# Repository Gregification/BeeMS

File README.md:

# BeeMS
Battery Management System (BMS)

__a work in progress__

BMS for University Of Texas At Arlington's FSAE Race team's E27 vehicle.
> point of contact for this repo is <a href="https://github.com/gregclacker"> George Boone</a>

## Development
- Code Composer Studio 12
    - dependency on Driver Lib
    - projects are stand alone, no dependencies on other projects in this repo.
- Kicad 9
    - common symbol and footprint library shared amongst all Kicad projects. "zzLocal".

---
<i>
    <a href="https://github.com/goerge">goerge (Gorge Albrecht)</a> is not in any way involved or associated with this project. that account was accidentally listed as a contributor because of a typo in the spelling of <a href="https://github.com/gregclacker">george (George Boone)</a>.
</i>

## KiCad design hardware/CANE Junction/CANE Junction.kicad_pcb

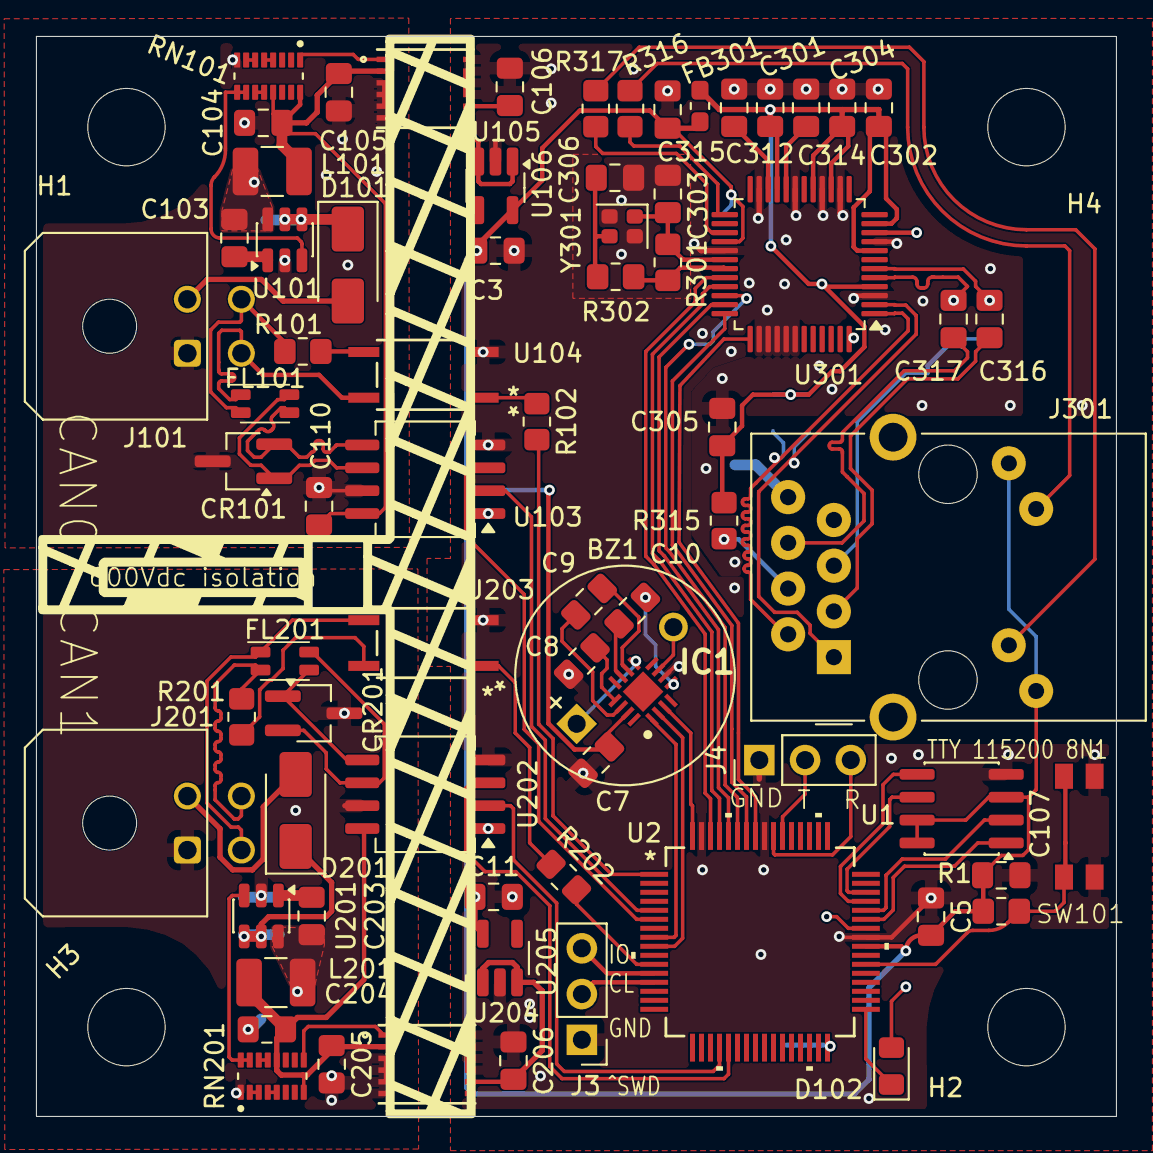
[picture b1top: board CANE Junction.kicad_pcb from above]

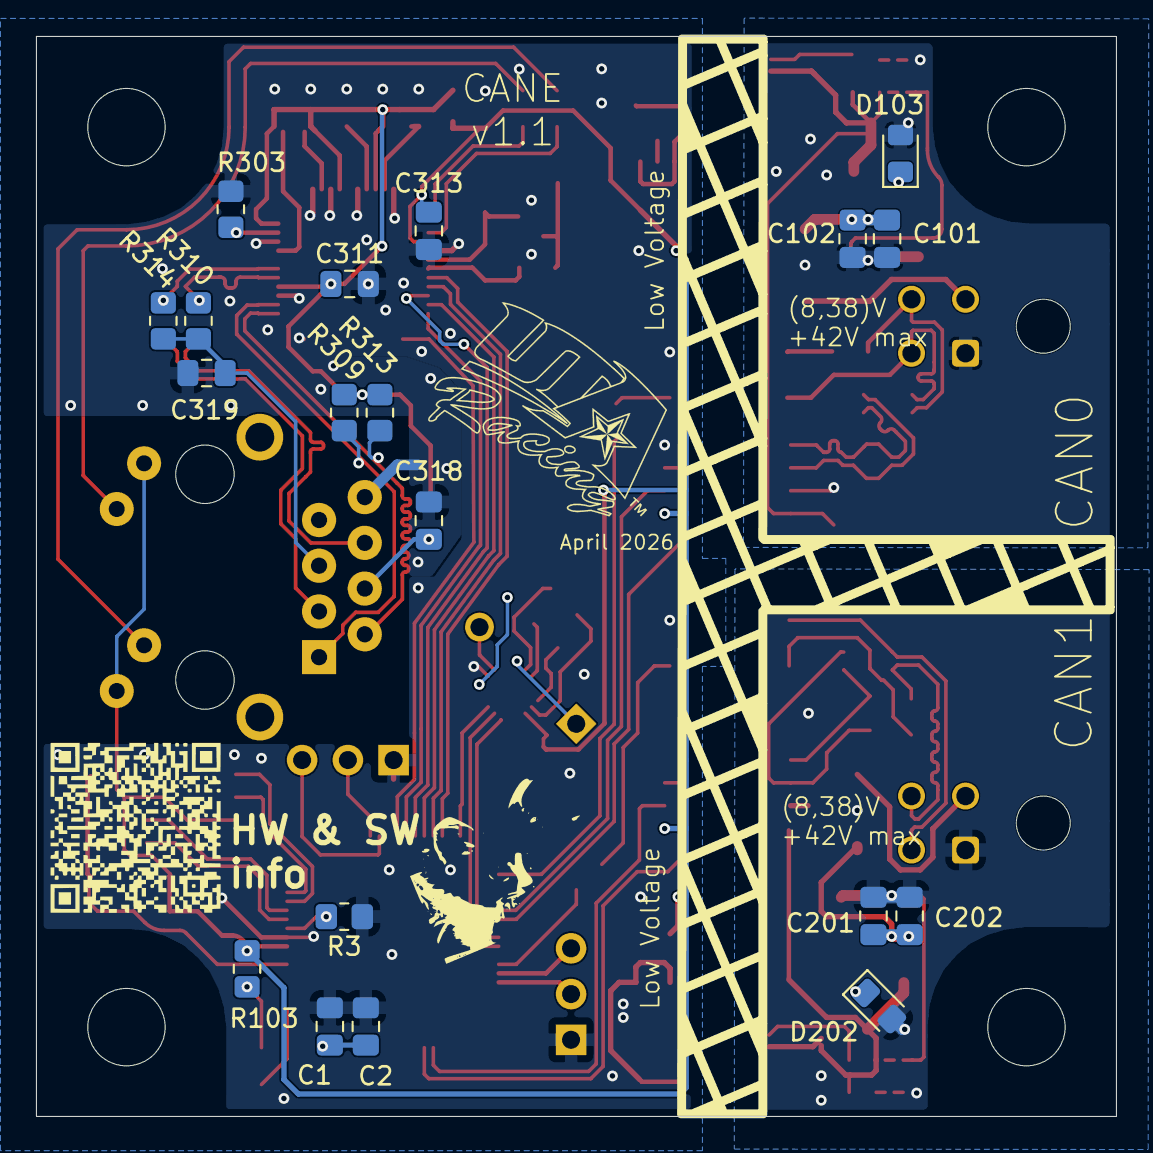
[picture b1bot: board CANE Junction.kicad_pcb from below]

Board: 2 copper layers, 60.0 x 60.0 mm, 95 parts (19 on the bottom side), 92 nets.

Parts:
BZ1: Buzzer; MagneticBuzzer_ProSignal_ABI-009-RC
C1, C2, C3, C11, C101, C102, C201, C202: 470n; C_0805_2012Metric_Pad1.18x1.45mm_HandSolder
C5, C7, C104, C105, C106, C204, C205, C206, C302: 22u; C_0805_2012Metric_Pad1.18x1.45mm_HandSolder
C8, C9, C10: 100n; C_0805_2012Metric_Pad1.18x1.45mm_HandSolder
C103, C107, C110, C203, C301, C304, C305, C311, C313, C315: 220n; C_0805_2012Metric_Pad1.18x1.45mm_HandSolder
C303, C306: 18p; C_0805_2012Metric_Pad1.18x1.45mm_HandSolder
C312, C319: 10n; C_0805_2012Metric_Pad1.18x1.45mm_HandSolder
C314: 4.7u; C_0805_2012Metric_Pad1.18x1.45mm_HandSolder
C316, C317: 6.8n; C_0805_2012Metric_Pad1.18x1.45mm_HandSolder
C318: 22n; C_0805_2012Metric_Pad1.18x1.45mm_HandSolder
CR101, CR201: ESD2CAN36DBZRQ1; TSOT-23_HandSoldering
D101, D201: ES1D; D_SMA
D102: blue; LED_0805_2012Metric_Pad1.15x1.40mm_HandSolder
D103, D202: TS4148; D_0805_2012Metric_Pad1.15x1.40mm_HandSolder
FB301: MH1608-151Y; L_0603_1608Metric_Pad1.05x0.95mm_HandSolder
FL101, FL201: Choke_CommonMode_FerriteCore_1243; L_CommonMode_Wurth_WE-CNSW-1206
H1, H2, H3, H4: MountingHole; MountingHole_4.3mm_M4_ISO7380
IC1: PAM8904QJER; QFN50P300X300X65-17N-D
J3: programming; PinHeader_1x03_P2.54mm_Vertical
J4: UART; PinHeader_1x03_P2.54mm_Vertical
J101, J201: glv; Molex_Micro-Fit_3.0_43045-0400_2x02_P3.00mm_Horizontal
J301: RJ45_Amphenol_RJMG1BD3B8K1ANR
L101, L201: 10u; L_1210_3225Metric_Pad1.42x2.65mm_HandSolder
R1, R3: 100k; R_0805_2012Metric_Pad1.20x1.40mm_HandSolder
R101, R201: 121; R_0805_2012Metric_Pad1.20x1.40mm_HandSolder
R102, R202, R316, R317: 750; R_0805_2012Metric_Pad1.20x1.40mm_HandSolder
R103: 2.4k; R_0805_2012Metric_Pad1.20x1.40mm_HandSolder
R301: 1M; R_0805_2012Metric_Pad1.20x1.40mm_HandSolder
R302, R315: 10; R_0805_2012Metric_Pad1.20x1.40mm_HandSolder
R303: 12.4k; R_0805_2012Metric_Pad1.20x1.40mm_HandSolder
R309, R310, R313, R314: 49.9; R_0805_2012Metric_Pad1.20x1.40mm_HandSolder
RN101, RN201: 20k; R_array_EXB2HV_8
SW101: SW_Push; wurth elektronik 4.7x3.5mm side push button
U1: MX25L3233FM2; SOIC-8_3.9x4.9mm_P1.27mm
U2: XMSPM0G3519SPMR; LQFP64_PM_TEX-M
U101, U201: AP64060ZQ; TSOT-23-6
U103, U202: ISO1044BD; SOIC-8_5.3x6.2mm_P1.27mm
U104, U203: ISOM8600; SOIC4_DFG_TEX-M
U105, U204: PUCC33420QRAQRQ1; VSON-FCRLF12_RAQ_TEX
U106, U205: NCP163ASN330T1G; SOT-23-5_HandSoldering
U301: W5500; LQFP-48_7x7mm_P0.5mm
Y301: Crystal_GND24; Crystal_SMD_2016-4Pin_2.0x1.6mm

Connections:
+3.3V: C3.1, C5.2, C7.1, C11.1, C107.2, C313.1, C315.1, FB301.1, IC1.15 (VIN), J301.L1, J301.L4, R1.1, R103.1, U1.3 (~WP/SIO2), U1.7 (~HOLD/SIO3), U1.8 (VCC), U2.40 (VDD), U103.1 (VCC1), U106.5 (VOUT), U202.1 (VCC1), U205.5 (VOUT), U301.28 (VDD)
/CAN interface 1/CAN+: FL101.1, J101.3, U104.4
/CAN interface 1/CAN-: FL101.4, J101.4, R101.1
/CAN interface 1/C_N: CR101.2, FL101.3, U103.5 (CANL)
/CAN interface 1/C_P: CR101.1, FL101.2, U103.6 (CANH)
/CAN interface 1/GLV_5v: C104.1, C105.1, C110.1, L101.1, RN101.13 (R4.2), RN101.16 (R1.2), U103.8 (VCC2), U105.2 (VINP)
/CAN interface 1/LV+: D101.2 (A), J101.2
/CAN interface 1/LV-: C101.2, C102.2, C104.2, C105.2, C110.2, CR101.3, D103.2 (A), J101.1, RN101.8 (R8.1), U101.2 (GND), U103.7 (GND2), U105.3 (GNDP), U105.4 (GNDP), U105.5 (GNDP), U105.6 (GNDP)
/CAN interface 2/CAN+: FL201.1, J201.3, U203.3
/CAN interface 2/CAN-: FL201.4, J201.4, R201.2
/CAN interface 2/C_N: CR201.1, FL201.3, U202.5 (CANL)
/CAN interface 2/C_P: CR201.2, FL201.2, U202.6 (CANH)
/CAN interface 2/GLV_5v: C204.1, C205.1, L201.1, RN201.8 (R8.1), RN201.12 (R5.2), U202.8 (VCC2), U204.2 (VINP)
/CAN interface 2/LV+: D201.2 (A), J201.2
/CAN interface 2/LV-: C201.2, C202.2, C204.2, C205.2, CR201.3, D202.2 (A), J201.1, RN201.1 (R1.1), U201.2 (GND), U202.7 (GND2), U204.3 (GNDP), U204.4 (GNDP), U204.5 (GNDP), U204.6 (GNDP)
/Ethernet/+3.3VA: C301.1, C302.1, C304.1, C305.1, C311.1, FB301.2, R309.2, R313.2, R315.1, U301.4 (AVDD), U301.8 (AVDD), U301.11 (AVDD), U301.15 (AVDD), U301.17 (AVDD), U301.21 (AVDD)
/Ethernet/RD+: C316.2, J301.R3 (RD+)
/Ethernet/RD-: C317.2, J301.R6 (RD-)
/Ethernet/RX+: C316.1, R314.2, U301.6 (RXP)
/Ethernet/RX-: C317.1, R310.2, U301.5 (RXN)
/Ethernet/TD+: J301.R1 (TD+), R309.1, U301.2 (TXP)
/Ethernet/TD-: J301.R2 (TD-), R313.1, U301.1 (TXN)
/SECD.MISO/POCI: U1.2 (SO/SIO1), U2.44 (PA4)
/SECD.MOSI/PICO: U1.5 (SI/SIO0), U2.45 (PA5)
/SECD.SCLK: U1.6 (SCLK), U2.46 (PA6)
/SECD.cs_fr: U1.1 (~CS), U2.43 (PA3)
/buzzer.pm1: IC1.1 (CPM1), U2.8 (PA15)
/buzzer.pm2: IC1.2 (CPM2), U2.9 (PA16)
/buzzer.pwm: IC1.3 (DIN), U2.64 (PB12)
/can0.RX: U2.6 (PA13), U103.3 (RXD)
/can0.TX: U2.5 (PA12), U103.2 (TXD)
/can0.term: R102.2, U2.1 (PB13)
/can1.RX: U2.21 (PB22), U202.3 (RXD)
/can1.TX: U2.20 (PB21), U202.2 (TXD)
/can1.term: R202.2, U2.11 (PA18)
/eth.MISO/POCI: U2.59 (PB7), U301.34 (MISO)
/eth.MOSI/PICO: U2.60 (PB8), U301.35 (MOSI)
/eth.SCLK: U2.61 (PB9), U301.33 (SCLK)
/eth.cs_N: U2.62 (PB10), U301.32 (~SCS)
/eth.irq_N: U2.58 (PB6), U301.36 (~INT)
/eth.reset_N: U2.57 (PA11), U301.37 (~RST)
/prog.SWCLK: J3.2, U2.13 (PA20)
/prog.SWDIO: J3.3, U2.12 (PA19)
/uart1.RX: J4.3, U2.55 (PA9)
/uart1.TX: J4.2, U2.54 (PA8)
GND: C1.2, C2.2, C3.2, C5.1, C7.2, C8.1, C11.2, C106.1, C107.1, C206.1, C301.2, C302.2, C303.2, C304.2, C305.2, C306.2, C311.2, C312.2, C313.2, C314.1, C315.2, C318.2, C319.2, IC1.6 (GND), J3.1, J4.1, J301.R8, R3.1, R303.2, SW101.2, U1.4 (GND), U2.41 (VSS), U2.56 (PA10), U2.63 (PB11), U103.4 (GND1), U104.2, U105.9 (GNDS), U105.10 (GNDS), U105.11 (GNDS), U105.12 (GNDS), U106.2 (GND), U202.4 (GND1), U203.2, U204.9 (GNDS), U204.10 (GNDS), U204.11 (GNDS), U204.12 (GNDS), U205.2 (GND), U301.3 (AGND), U301.9 (AGND), U301.14 (AGND), U301.16 (AGND), U301.19 (AGND), U301.23 (RSVD), U301.29 (GND), U301.38 (RSVD), U301.39 (RSVD), U301.40 (RSVD), U301.41 (RSVD), U301.42 (RSVD), U301.48 (AGND), Y301.2, Y301.4
unnamed: BZ1.1 (+), IC1.9 (VO1)
unnamed: BZ1.2 (-), IC1.7 (VO2)
unnamed: C306.1, R302.1, Y301.3
unnamed: C101.1, C102.1, D101.1 (K), U101.4 (EN), U101.5 (Vin)
unnamed: D102.2 (A), R103.2
unnamed: D102.1 (K), U2.33 (PA0)
unnamed: C103.2, D103.1 (K), L101.2, U101.6 (SW)
unnamed: C201.1, C202.1, D201.1 (K), U201.4 (EN), U201.5 (Vin)
unnamed: C203.2, D202.1 (K), L201.2, U201.6 (SW)
unnamed: C10.2, IC1.5 (CN1)
unnamed: C9.2, IC1.10 (CN2)
unnamed: C10.1, IC1.11 (CP1)
unnamed: C9.1, IC1.14 (CP2)
unnamed: C8.2, IC1.13 (VOUT)
unnamed: J301.L2, R316.2
unnamed: J301.L3, R317.2
unnamed: C319.1, J301.R5 (RCT), R310.1, R314.1
unnamed: C318.1, J301.R4 (TCT), R315.2
unnamed: R101.2, U104.3
unnamed: R102.1, U104.1
unnamed: R201.1, U203.4
unnamed: R202.1, U203.1
unnamed: RN101.1 (R1.1), U105.1 (EN/FLT)
unnamed: RN101.4 (R4.1), RN101.5 (R5.1)
unnamed: RN101.11 (R6.2), RN101.12 (R5.2)
unnamed: RN101.6 (R6.1), RN101.7 (R7.1)
unnamed: RN101.9 (R8.2), RN101.10 (R7.2), U101.3 (FB)
unnamed: RN201.15 (R2.2), RN201.16 (R1.2), U201.3 (FB)
unnamed: RN201.2 (R2.1), RN201.3 (R3.1)
unnamed: RN201.13 (R4.2), RN201.14 (R3.2)
unnamed: RN201.4 (R4.1), RN201.5 (R5.1)
unnamed: RN201.9 (R8.2), U204.1 (EN/FLT)
unnamed: R1.2, SW101.1, U2.38 (NRST)
unnamed: R3.2, U2.42 (PA2)
unnamed: C1.1, C2.1, U2.32 (VCORE)
unnamed: C103.1, U101.1 (BST)
unnamed: C106.2, U105.7 (SEL), U105.8 (VCC), U106.1 (VIN), U106.3 (EN)
unnamed: C203.1, U201.1 (BST)
unnamed: C206.2, U204.7 (SEL), U204.8 (VCC), U205.1 (VIN), U205.3 (EN)
unnamed: C312.1, U301.22 (1V2O)
unnamed: R317.1, U301.27 (ACTLED)
unnamed: R303.1, U301.10 (EXRES1)
unnamed: R316.1, U301.25 (LINKLED)
unnamed: C314.2, U301.20 (TOCAP)
unnamed: C303.1, R301.1, U301.30 (XI/CLKIN), Y301.1
unnamed: R301.2, R302.2, U301.31 (XO)

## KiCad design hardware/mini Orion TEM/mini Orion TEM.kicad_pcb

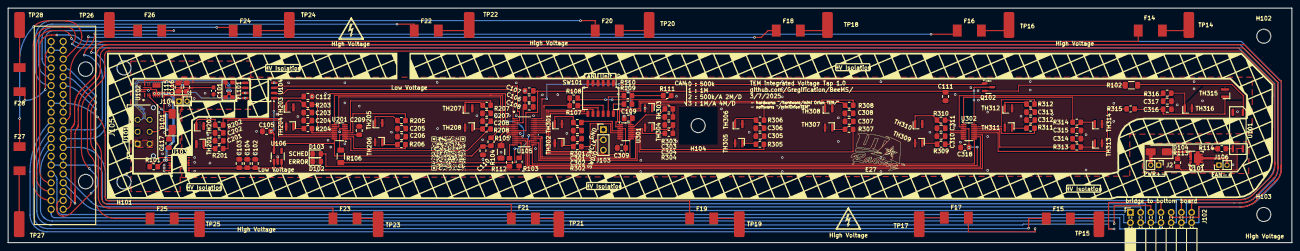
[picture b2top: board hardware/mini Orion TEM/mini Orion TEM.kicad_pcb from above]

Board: 2 copper layers, 319.7 x 58.4 mm, 163 parts (0 on the bottom side), 148 nets.

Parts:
C101: 1u; C_0603_1608Metric_Pad1.08x0.95mm_HandSolder
C102, C104, C105, C107, C110, C111, C115, C116: 22u; C_0805_2012Metric_Pad1.18x1.45mm_HandSolder
C103, C106, C108, C109, C112, C117, C201, C202, C203, C204, C205, C206, C207, C208, C209, C301, C302, C303, C304, C305, C306, C307, C308, C309, C310, C311, C312, C313, C314, C315, C316, C317, C318: 220n; C_0805_2012Metric_Pad1.18x1.45mm_HandSolder
D101, D104: ES1D; D_SMA
D102: blue; LED_0805_2012Metric_Pad1.15x1.40mm_HandSolder
D103: red; LED_0805_2012Metric_Pad1.15x1.40mm_HandSolder
F14, F15, F16, F17, F18, F19, F20, F21, F22, F23, F24, F25, F26, F27, F28: 1.5A; yageo fuse 6.1x2.5mm midplane
FL101: Choke_CommonMode_FerriteCore_1243; L_CommonModeChoke_Coilcraft_1812CAN
H101, H102, H103, H104, H105: MountingHole; MountingHole_3.5mm
J2: Fan enable; PinHeader_1x02_P2.00mm_Vertical
J101: HRLV; Molex_Micro-Fit_3.0_43045-0612_2x03_P3.00mm_Vertical
J102: bridge to bottom board; PinSocket_2x07_P2.54mm_Horizontal
J103: SWD; PinHeader_1x03_P2.54mm_Vertical
J104: fan pwr source; PinHeader_1x02_P2.00mm_Vertical
J105: VT harness; 13761132
J106: fan PWR; PinHeader_1x02_P2.00mm_Vertical
Q101: DI035P04PT; D_QFN_3.3x3.3mm_P0.65mm
Q102: MMBT5550L; SOT-23
R101, R105, R108, R111: 22.1k; R_0805_2012Metric_Pad1.20x1.40mm_HandSolder
R102: 332; R_1206_3216Metric_Pad1.30x1.75mm_HandSolder
R103, R112, R201, R202, R203, R204, R205, R206, R207, R208, R301, R302, R303, R304, R305, R306, R307, R308, R309, R310, R311, R312, R313, R314, R315, R316: 2.4k; R_0805_2012Metric_Pad1.20x1.40mm_HandSolder
R104: 100k; R_1206_3216Metric_Pad1.30x1.75mm_HandSolder
R106: JUMPER 4.7; R_1206_3216Metric_Pad1.30x1.75mm_HandSolder
R107, R109, R110, R113, R114: 40.2k; R_0805_2012Metric_Pad1.20x1.40mm_HandSolder
SW101: SW_DIP_x06; SW_DIP_SPSTx06_Slide_Copal_CHS-06B_W7.62mm_P1.27mm
TH201, TH202, TH203, TH204, TH205, TH206, TH207, TH208, TH301, TH302, TH303, TH304, TH305, TH306, TH307, TH308, TH309, TH310, TH311, TH312, TH313, TH314, TH315, TH316: Thermistor_US; FPC thermistor strip 2x2mm
TP14, TP15, TP16, TP17, TP18, TP19, TP20, TP21, TP22, TP23, TP24, TP25, TP26, TP27, TP28: Cell Tap; pad 2.667x6.472mm
U101: ISOM8110DFS; ISOM811_SOIC-4_DFG
U102: TPSM33606S5QRDNRQ1; RDN0011A_TEX
U103: PUCC33420QRAQRQ1; VSON-FCRLF12_RAQ_TEX
U104: ISO1044BD; SOIC-8_5.3x5.3mm_P1.27mm
U105: XMSM0G3507SDGS28R; VSSOP28_DGS_TEX-M
U106: NCP163ASN330T1G; SOT-23-5_HandSoldering
U201, U301, U302: SN74LV4051A-Q1; Texas_DYY0016A_TSOT-23-16_2x4.2mm_P0.5mm

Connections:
+3V3: C105.1, C107.1, C109.1, C110.1, C111.1, C112.2, Q102.3 (C), R105.2, U104.1 (VCC1), U105.7 (VDD), U106.5 (VOUT), U201.16 (VCC), U301.16 (VCC), U302.16 (VCC)
/HRLV_5v: C115.1, C116.1, R101.1, U102.4 (VOUT), U102.9 (FB), U103.2 (VINP), U104.8 (VCC2)
/HRLV_CAN+: FL101.4, J101.6
/HRLV_CAN-: FL101.1, J101.3
/HRLV_FAN+: J106.2, Q101.1 (D)
/HRLV_FAN-: J2.1, J106.1, R114.1
/HRLV_FAN_PRW+: D104.2 (A), J2.2
/HRLV_GLV+: D101.2 (A), J101.5, J104.2
/HRLV_GLV-: C101.2, C115.2, C116.2, C117.2, J101.2, J104.1, U102.10 (GND), U102.11 (MODE/SYNCH), U103.3 (GNDP), U103.4 (GNDP), U103.5 (GNDP), U103.6 (GNDP), U104.7 (GND2)
/HRLV_IL+: J101.1, J101.4
/LV_FAN_PWM: Q102.1 (B), U105.28 (PA25/A0_2)
/LV_LED_BLUE: R103.1, U105.13 (PA6/HFCLK_IN/HFXOUT)
/LV_LED_RED: R112.1, U105.14 (PA9_/_RTC_OUT_/_CLK_OUT)
/LV_SWCLK: J103.2, U105.23 (PA20/SWCLK)
/LV_SWDIO: J103.3, U105.22 (PA19/SWDIO)
/LV_TB1_A: U105.10 (PA3_/_LFXIN), U201.11 (A)
/LV_TB1_Aout: R106.1, U105.20 (PA17/A1_2)
/LV_TB1_B: U105.5 (PA1), U201.10 (B)
/LV_TB1_C: U105.4 (PA0), U201.9 (C)
/LV_TB2_A: U105.16 (PA11), U301.11 (A)
/LV_TB2_Aout: C309.1, U105.21 (PA18/A1_3), U301.3 (X)
/LV_TB2_B: U105.18 (PA15/A1_0), U301.10 (B)
/LV_TB2_C: U105.19 (PA16/A1_1/FCC_IN), U301.9 (C)
/LV_TB3_A: U105.12 (PA5/HFXIN/FCC_IN), U302.11 (A)
/LV_TB3_Aout: C318.1, U105.17 (PA14/CLK_OUT/A0_12), U302.3 (X)
/LV_TB3_B: U105.11 (PA4_/_LFCLK_IN_/_LFXOUT), U302.10 (B)
/LV_TB3_C: U105.15 (PA10/CLK_OUT), U302.9 (C)
/LV_sw_can_baud_1: SW101.7, U105.24 (PA21/A1_7/VREF-)
/LV_sw_can_baud_2: SW101.8, U105.25 (PA22/CLK_OUT/A0_7)
/LV_sw_r2r: R107.1, R108.2, U105.27 (PA24/A0_3)
/LV_sw_unit_id_1: SW101.9, U105.26 (PA23/VREF+)
/LV_sw_unit_id_2: R107.2, SW101.10
/LV_sw_unit_id_3: R110.2, SW101.11
/LV_sw_unit_id_4: R109.2, SW101.12
/VT1: J102.9, J105.1
/VT2: J102.10, J105.22
/VT3: J102.11, J105.2
/VT4: J102.12, J105.23
/VT5: J102.13, J105.3
/VT6: J102.14, J105.24
/VT7: J102.1, J105.4
/VT8: J102.2, J105.25
/VT9: J102.3, J105.5
/VT10/-13: J102.4, J105.6, J105.7, J105.26, J105.27
/VT13: J102.5, J105.28
/VT14: J102.6, J105.8
/VT15: J102.7, J105.29
/VT16: F14.1, J105.9
/VT17: F15.1, J105.30
/VT18: F16.1, J105.10
/VT19: F17.1, J105.31
/VT20: F18.1, J105.11
/VT21/-25: F19.1, J105.12, J105.13, J105.14, J105.32, J105.33
/VT25: F20.1, J105.35
/VT26: F21.1, J105.15
/VT27: F22.1, J105.36
/VT28: F23.1, J105.16
/VT29: F24.1, J105.37
/VT30: F25.1, J105.17
/VT31: F26.1, J105.38
/VT32: F27.1, J105.18
/VT33/36: F28.1, J105.19, J105.20, J105.39, J105.40
/VT-1: J102.8, J105.21
/thermistor bank 1/Aout1: C209.1, R106.2, U201.3 (X)
GND: C102.2, C103.2, C104.1, C105.2, C106.2, C107.2, C108.2, C109.2, C110.2, C111.2, C112.1, C201.2, C202.2, C203.2, C204.2, C205.2, C206.2, C207.2, C208.2, C209.2, C301.2, C302.2, C303.2, C304.2, C305.2, C306.2, C307.2, C308.2, C309.2, C310.2, C311.2, C312.2, C313.2, C314.2, C315.2, C316.2, C317.2, C318.2, D102.1 (K), D103.1 (K), J103.1, R104.2, SW101.1, SW101.2, SW101.3, SW101.4, SW101.5, SW101.6, TH201.2, TH202.2, TH203.2, TH204.2, TH205.2, TH206.2, TH207.2, TH208.2, TH301.2, TH302.2, TH303.2, TH304.2, TH305.2, TH306.2, TH307.2, TH308.2, TH309.2, TH310.2, TH311.2, TH312.2, TH313.2, TH314.2, TH315.2, TH316.2, U101.2 (-TX), U103.9 (GNDS), U103.10 (GNDS), U103.11 (GNDS), U103.12 (GNDS), U104.4 (GND1), U105.8 (VSS), U106.2 (GND), U201.6 (Inh), U201.7 (GND), U201.8 (GND), U301.6 (Inh), U301.7 (GND), U301.8 (GND), U302.6 (Inh), U302.7 (GND), U302.8 (GND)
unnamed: C201.1, R201.1, TH201.1
unnamed: C202.1, R202.1, TH202.1
unnamed: C203.1, R203.1, TH203.1
unnamed: C204.1, R204.1, TH204.1
unnamed: C205.1, R205.1, TH205.1
unnamed: C206.1, R206.1, TH206.1
unnamed: C207.1, R207.1, TH207.1
unnamed: C208.1, R208.1, TH208.1
unnamed: C301.1, R301.1, TH301.1
unnamed: C302.1, R302.1, TH302.1
unnamed: C303.1, R303.1, TH303.1
unnamed: C304.1, R304.1, TH304.1
unnamed: C305.1, R305.1, TH305.1
unnamed: C306.1, R306.1, TH306.1
unnamed: C307.1, R307.1, TH307.1
unnamed: C308.1, R308.1, TH308.1
unnamed: C310.1, R309.1, TH309.1
unnamed: C311.1, R310.1, TH310.1
unnamed: C312.1, R311.1, TH311.1
unnamed: C313.1, R312.1, TH312.1
unnamed: C314.1, R313.1, TH313.1
unnamed: C315.1, R314.1, TH314.1
unnamed: C316.1, R315.1, TH315.1
unnamed: C317.1, R316.1, TH316.1
unnamed: C117.1, D101.1 (K), U102.2 (EN), U102.3 (VIN)
unnamed: D102.2 (A), R103.2
unnamed: D103.2 (A), R112.2
unnamed: D104.1 (K), Q101.2 (S), R113.2
unnamed: F14.2, TP14.1
unnamed: F15.2, TP15.1
unnamed: F16.2, TP16.1
unnamed: F17.2, TP17.1
unnamed: F18.2, TP18.1
unnamed: F19.2, TP19.1
unnamed: F20.2, TP20.1
unnamed: F21.2, TP21.1
unnamed: F22.2, TP22.1
unnamed: F23.2, TP23.1
unnamed: F24.2, TP24.1
unnamed: F25.2, TP25.1
unnamed: F26.2, TP26.1
unnamed: F27.2, TP27.1
unnamed: F28.2, TP28.1
unnamed: Q101.3 (G), R113.1, U101.4 (C)
unnamed: Q102.2 (E), R102.1
unnamed: R108.1, R109.1, R111.2
unnamed: R110.1, R111.1
unnamed: R102.2, U101.1 (+TX)
unnamed: R114.2, U101.3 (E)
unnamed: C101.1, U102.8 (VCC)
unnamed: R101.2, U103.1 (EN/FLT)
unnamed: C102.1, C103.1, C104.2, U103.7 (SEL), U103.8 (VCC), U106.1 (VIN), U106.3 (EN)
unnamed: FL101.3, U104.6 (CANH)
unnamed: FL101.2, U104.5 (CANL)
unnamed: U104.3 (RXD), U105.2 (PA27/RTC_OUT/A0_0)
unnamed: U104.2 (TXD), U105.1 (PA26/A0_1)
unnamed: R105.1, U105.6 (NRST)
unnamed: R104.1, U105.9 (PA2_/_ROSC)
unnamed: C106.1, C108.1, U105.3 (VCORE)
unnamed: R204.2, U201.13 (X0)
unnamed: R202.2, U201.14 (X1)
unnamed: R201.2, U201.15 (X2)
unnamed: R203.2, U201.12 (X3)
unnamed: R208.2, U201.1 (X4)
unnamed: R207.2, U201.5 (X5)
unnamed: R206.2, U201.2 (X6)
unnamed: R205.2, U201.4 (X7)
unnamed: R305.2, U301.13 (X0)
unnamed: R304.2, U301.14 (X1)
unnamed: R303.2, U301.15 (X2)
unnamed: R307.2, U301.12 (X3)
unnamed: R306.2, U301.1 (X4)
unnamed: R302.2, U301.5 (X5)
unnamed: R308.2, U301.2 (X6)
unnamed: R301.2, U301.4 (X7)
unnamed: R313.2, U302.13 (X0)
unnamed: R311.2, U302.14 (X1)
unnamed: R312.2, U302.15 (X2)
unnamed: R315.2, U302.12 (X3)
unnamed: R314.2, U302.1 (X4)
unnamed: R309.2, U302.5 (X5)
unnamed: R316.2, U302.2 (X6)
unnamed: R310.2, U302.4 (X7)

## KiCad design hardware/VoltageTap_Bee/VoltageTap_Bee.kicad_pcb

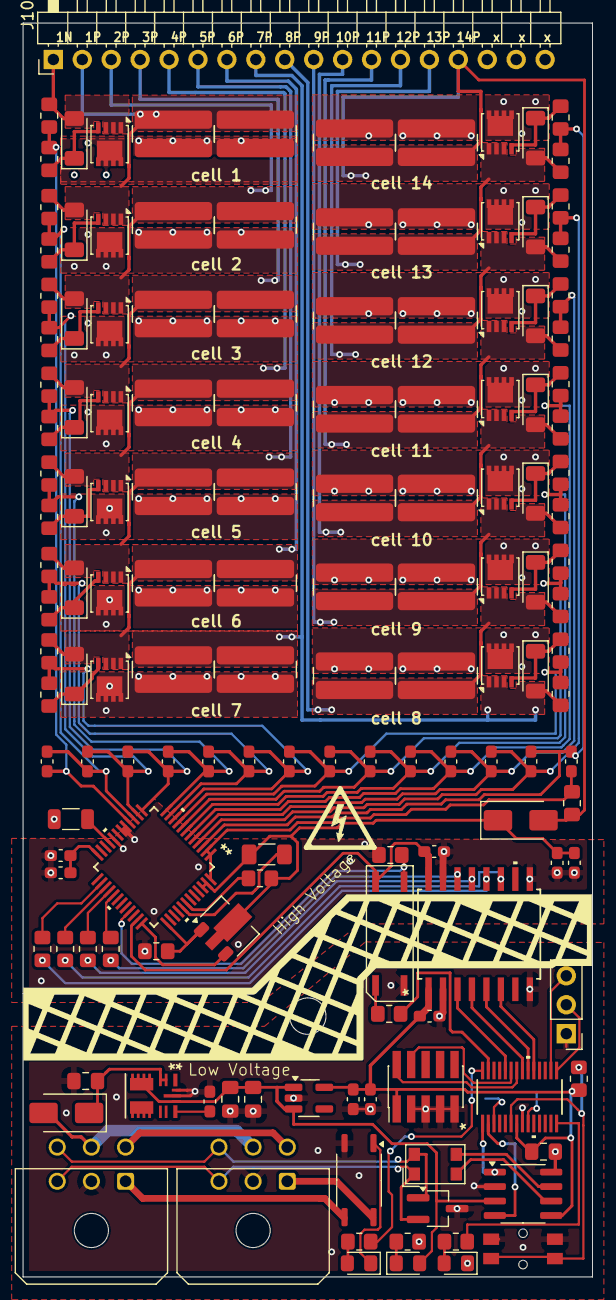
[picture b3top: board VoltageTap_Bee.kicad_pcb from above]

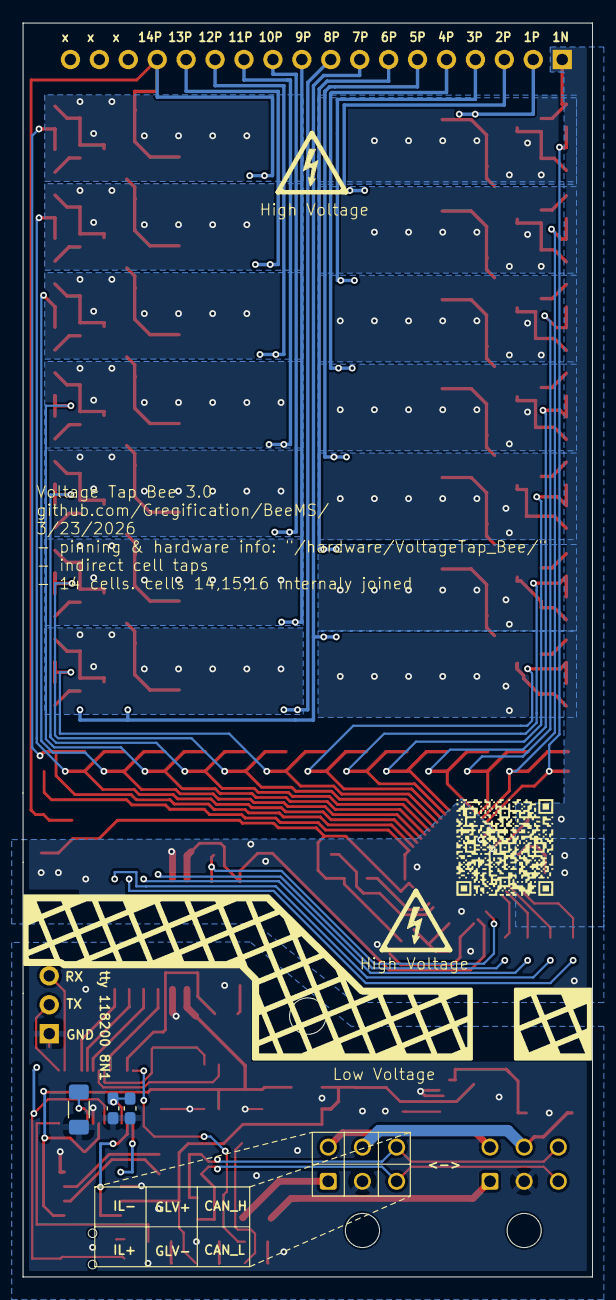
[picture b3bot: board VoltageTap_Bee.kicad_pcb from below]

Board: 2 copper layers, 50.0 x 110.1 mm, 152 parts (3 on the bottom side), 109 nets.

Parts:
C101: 220n; C_0805_2012Metric_Pad1.18x1.45mm_HandSolder
C102, C217, C218, C219, C220: 1u; C_0603_1608Metric_Pad1.08x0.95mm_HandSolder
C103, C104, C106: 22u; C_0805_2012Metric_Pad1.18x1.45mm_HandSolder
C105, C107, C108, C109, C110, C111, C201, C202, C203, C204, C205, C206, C207, C210, C211, C212, C213, C214, C215, C216: 100n; C_0603_1608Metric_Pad1.08x0.95mm_HandSolder
CR101: ESD2CAN36DBZRQ1; TSOT-23_HandSoldering
D101, D215: ES1D; D_SMA
D102: green; LED_0805_2012Metric_Pad1.15x1.40mm_HandSolder
D103: blue; LED_0805_2012Metric_Pad1.15x1.40mm_HandSolder
D104: yellow; LED_0805_2012Metric_Pad1.15x1.40mm_HandSolder
D201, D202, D203, D204, D205, D206, D207, D208, D209, D210, D211, D212, D213, D214: 13V; D_MiniMELF
FL101: Choke_CommonMode_FerriteCore_1243; L_CommonModeChoke_Coilcraft_1812CAN
H101: MountingHole; MountingHole_3.2mm_M3
J101: VT; PinHeader_1x18_P2.54mm_Horizontal
J102: HRLV daisy A; Molex_Micro-Fit_3.0_43045-0600_2x03_P3.00mm_Horizontal
J103: HRLV daisy B; Molex_Micro-Fit_3.0_43045-0600_2x03_P3.00mm_Horizontal
J104: Conn_02x05_Odd_Even; PinHeader_2x05_P1.27mm_Vertical_SMD
J105: uart; PinHeader_1x03_P2.54mm_Vertical
Q201, Q202, Q203, Q204, Q205, Q206, Q207, Q208, Q209, Q210, Q211, Q212, Q213, Q214: SiSA96DN; Vishay_PowerPAK_1212-8_Single
R101, R102, R103, R104, R106, R107, R108, R109, R216, R218, R220, R222, R224, R226, R228, R245, R247, R249, R251, R253, R255, R257: 3.32k; R_0805_2012Metric_Pad1.20x1.40mm_HandSolder
R105, R110, R261, R263: 10k; R_0805_2012Metric_Pad1.20x1.40mm_HandSolder
R111: 100k; R_1206_3216Metric_Pad1.30x1.75mm_HandSolder
R201, R202, R203, R204, R205, R206, R207, R208, R209, R210, R211, R212, R213, R214, R229, R230, R231, R232, R233, R234, R235, R238, R239, R240, R241, R242, R243, R244: 15; imperial wide resistor R_ 3264
R215, R217, R219, R221, R223, R225, R227, R246, R248, R250, R252, R254, R256, R258, R259: 100; R_0805_2012Metric_Pad1.20x1.40mm_HandSolder
R262: 4.99k; R_1206_3216Metric_Pad1.30x1.75mm_HandSolder
SW101: SW_Push; wurth elektronik 4.7x3.5mm side push button
TH107: Thermistor; R_1206_3216Metric
U101: TPSM33606S5QRDNRQ1; RDN0011A_TEX
U102: TLP176AM; SOIC-4_4.55x3.7mm_P2.54mm
U103: ISOM8110DFS; ISOM811_SOIC-4_DFG
U104: NCP163ASN330T1G; SOT-23-5_HandSoldering
U105: XISO6441DWR; SOIC16_DW_TEX-M
U106: MCP2542FDxMF; SOIC-8_3.9x4.9mm_P1.27mm
U107: XMSM0G3507SDGS28R; VSSOP28_DGS_TEX-M
U201: PBQ76952PFBT; BQ76952_PFB48_TEX
U203: FCX495; SOT-89-3

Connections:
+3.3V: C106.1, C107.1, C110.1, C111.1, J104.1, R110.2, U104.5 (VOUT), U105.1 (VCC1), U106.5 (VIO), U107.7 (VDD)
+5V: C103.1, C104.1, D104.2 (A), U101.4 (VOUT), U101.9 (FB), U104.1 (VIN), U104.3 (EN), U106.3 (VDD)
+BATT: D215.2 (A), J101.15, R201.2, R208.2, R215.2
-BATT: C105.2, C217.2, C218.2, C219.2, C220.2, D214.2 (A), J101.1, Q214.1 (S), Q214.2 (S), Q214.3 (S), R105.1, R258.2, R263.2, TH107.2, U105.9 (GND2), U105.15 (GND2), U201.17 (VSS), U201.18 (SRP), U201.20 (SRN)
/BQ0_3.3v: C105.1, U103.4 (C), U105.16 (VCC2), U201.35 (REG1)
/BQ76952 1/1P: D213.2 (A), J101.2, Q213.1 (S), Q213.2 (S), Q213.3 (S), R235.2, R244.2, R256.2
/BQ76952 1/2P: D201.2 (A), J101.3, Q212.1 (S), Q212.2 (S), Q212.3 (S), R234.2, R243.2, R254.2
/BQ76952 1/3P: D202.2 (A), J101.4, Q211.1 (S), Q211.2 (S), Q211.3 (S), R233.2, R242.2, R252.2
/BQ76952 1/4P: D203.2 (A), J101.5, Q210.1 (S), Q210.2 (S), Q210.3 (S), R232.2, R241.2, R250.2
/BQ76952 1/5P: D204.2 (A), J101.6, Q209.1 (S), Q209.2 (S), Q209.3 (S), R231.2, R240.2, R248.2
/BQ76952 1/6P: D205.2 (A), J101.7, Q208.1 (S), Q208.2 (S), Q208.3 (S), R230.2, R239.2, R246.2
/BQ76952 1/7P: D212.2 (A), J101.8, Q207.1 (S), Q207.2 (S), Q207.3 (S), R229.2, R238.2, R259.2
/BQ76952 1/8P: D211.2 (A), J101.9, Q206.1 (S), Q206.2 (S), Q206.3 (S), R207.2, R214.2, R227.2
/BQ76952 1/9P: D210.2 (A), J101.10, Q205.1 (S), Q205.2 (S), Q205.3 (S), R206.2, R213.2, R225.2
/BQ76952 1/10P: D209.2 (A), J101.11, Q204.1 (S), Q204.2 (S), Q204.3 (S), R205.2, R212.2, R223.2
/BQ76952 1/11P: D208.2 (A), J101.12, Q203.1 (S), Q203.2 (S), Q203.3 (S), R204.2, R211.2, R221.2
/BQ76952 1/12P: D207.2 (A), J101.13, Q202.1 (S), Q202.2 (S), Q202.3 (S), R203.2, R210.2, R219.2
/BQ76952 1/13P: D206.2 (A), J101.14, Q201.1 (S), Q201.2 (S), Q201.3 (S), R202.2, R209.2, R217.2
/BQ76952 1/BAT: C218.1, C219.1, D215.1 (K), R261.2, R262.1, U201.46 (CP1), U201.47 (BAT), U203.2
/BQ76952 1/C1Jc: Q214.5 (D), R235.1, R244.1
/BQ76952 1/C2Jc: Q213.5 (D), R234.1, R243.1
/BQ76952 1/C3Jc: Q212.5 (D), R233.1, R242.1
/BQ76952 1/C4Jc: Q211.5 (D), R232.1, R241.1
/BQ76952 1/C5Jc: Q210.5 (D), R231.1, R240.1
/BQ76952 1/C6Jc: Q209.5 (D), R230.1, R239.1
/BQ76952 1/C7Jc: Q208.5 (D), R229.1, R238.1
/BQ76952 1/C8Jc: Q207.5 (D), R207.1, R214.1
/BQ76952 1/C9Jc: Q206.5 (D), R206.1, R213.1
/BQ76952 1/C10Jc: Q205.5 (D), R205.1, R212.1
/BQ76952 1/C11Jc: Q204.5 (D), R204.1, R211.1
/BQ76952 1/C12Jc: Q203.5 (D), R203.1, R210.1
/BQ76952 1/C13Jc: Q202.5 (D), R202.1, R209.1
/BQ76952 1/C14Jc: Q201.5 (D), R201.1, R208.1
/BQ76952 1/CFETOFF: R101.1, U201.29 (CFETOFF)
/BQ76952 1/HDQ: R102.1, U201.28 (HDQ)
/BQ76952 1/RST_SHUT: R105.2, U103.3 (E), U201.33 (RST_SHUT)
/BQ76952 1/SCL: R103.1, U201.26 (SCL)
/BQ76952 1/SDA: R104.1, U201.27 (SDA)
/BQ76952 1/TS1: TH107.1, U201.21 (TS1)
/CAN+: CR101.1 (IO), FL101.4, J102.6, J103.6
/CAN-: CR101.2 (IO), FL101.1, J102.3, J103.3
/GLV+: D101.2 (A), J102.5, J103.5
/IL EN: R106.2, U107.28 (PA25/A0_2)
/IL_A+: J102.1, U102.6
/IL_A-: J102.4, J103.4
/IL_B+: J103.1, U102.4
/MCU_RESET: R110.1, SW101.2, U107.6 (NRST)
/bbqCS: U105.3 (INA), U107.24 (PA21/A1_7/VREF-)
/bbqrst: R107.2, U107.27 (PA24/A0_3)
/led.sched: R108.1, U107.14 (PA9_/_RTC_OUT_/_CLK_OUT)
GND: C101.2, C102.2, C103.2, C104.2, C106.2, C107.2, C108.2, C109.2, C110.2, C111.2, CR101.3 (GND), D103.1 (K), J102.2, J103.2, J104.3, J104.5, J104.7, J104.9, J105.1, R109.1, R111.2, SW101.1, U101.10 (GND), U101.11 (MODE/SYNCH), U102.3, U103.2 (-TX), U104.2 (GND), U105.2 (GND1), U105.8 (GND1), U106.2 (VSS), U106.8 (STBY), U107.8 (VSS)
unnamed: C101.1, D101.1 (K), U101.2 (EN), U101.3 (VIN)
unnamed: D102.2 (A), R106.1
unnamed: D102.1 (K), U102.1
unnamed: D103.2 (A), R108.2
unnamed: D104.1 (K), R109.2
unnamed: D201.1 (K), Q212.4 (G), R253.1
unnamed: D202.1 (K), Q211.4 (G), R251.1
unnamed: D203.1 (K), Q210.4 (G), R249.1
unnamed: D204.1 (K), Q209.4 (G), R247.1
unnamed: D205.1 (K), Q208.4 (G), R245.1
unnamed: D206.1 (K), Q201.4 (G), R216.1
unnamed: D207.1 (K), Q202.4 (G), R218.1
unnamed: D208.1 (K), Q203.4 (G), R220.1
unnamed: D209.1 (K), Q204.4 (G), R222.1
unnamed: D210.1 (K), Q205.4 (G), R224.1
unnamed: D211.1 (K), Q206.4 (G), R226.1
unnamed: D212.1 (K), Q207.4 (G), R228.1
unnamed: D213.1 (K), Q213.4 (G), R255.1
unnamed: D214.1 (K), Q214.4 (G), R257.1
unnamed: C102.1, U101.8 (VCC)
unnamed: R107.1, U103.1 (+TX)
unnamed: R104.2, U105.11 (IND)
unnamed: R101.2, U105.14 (OUTA)
unnamed: R102.2, U105.13 (OUTB)
unnamed: R103.2, U105.12 (OUTC)
unnamed: FL101.3, U106.7 (CANH)
unnamed: FL101.2, U106.6 (CANL)
unnamed: R111.1, U107.9 (PA2_/_ROSC)
unnamed: C108.1, C109.1, U107.3 (VCORE)
unnamed: R263.1, U201.37 (BREG), U203.1
unnamed: R262.2, U201.41 (LD)
unnamed: R261.1, U201.42 (PACK)
unnamed: C217.1, C220.1, U201.24 (REG18)
unnamed: U201.36 (REGIN), U203.3
unnamed: C216.2, R257.2, R258.1, U201.16 (VC0)
unnamed: C215.2, C216.1, R255.2, R256.1, U201.15 (VC1)
unnamed: C214.2, C215.1, R253.2, R254.1, U201.14 (VC2)
unnamed: C213.2, C214.1, R251.2, R252.1, U201.13 (VC3)
unnamed: C212.2, C213.1, R249.2, R250.1, U201.12 (VC4)
unnamed: C211.2, C212.1, R247.2, R248.1, U201.11 (VC5)
unnamed: C210.2, C211.1, R245.2, R246.1, U201.10 (VC6)
unnamed: C207.2, C210.1, R228.2, R259.1, U201.9 (VC7)
unnamed: C206.2, C207.1, R226.2, R227.1, U201.8 (VC8)
unnamed: C205.2, C206.1, R224.2, R225.1, U201.7 (VC9)
unnamed: C204.2, C205.1, R222.2, R223.1, U201.6 (VC10)
unnamed: C203.2, C204.1, R220.2, R221.1, U201.5 (VC11)
unnamed: C202.2, C203.1, R218.2, R219.1, U201.4 (VC12)
unnamed: C201.2, C202.1, R216.2, R217.1, U201.3 (VC13)
unnamed: C201.1, R215.1, U201.1 (VC15), U201.2 (VC14), U201.48 (VC16)
PA10_UART0-TX_XDS: J105.2, U107.15 (PA10/CLK_OUT)
PA11_UART0-RX_XDS: J105.3, U107.16 (PA11)
PA16_SPI1_MISO: U105.6 (OUTD), U107.19 (PA16/A1_1/FCC_IN)
PA17_SPI1_SCK: U105.5 (INC), U107.20 (PA17/A1_2)
PA18_SPI1_MOSI: U105.4 (INB), U107.21 (PA18/A1_3)
PA19_SWDIO: J104.2, U107.22 (PA19/SWDIO)
PA20_SWCLK: J104.4, U107.23 (PA20/SWCLK)
PA26_CAN_TX: U106.1 (TXD), U107.1 (PA26/A0_1)
PA27_CAN_RX: U106.4 (RXD), U107.2 (PA27/RTC_OUT/A0_0)
